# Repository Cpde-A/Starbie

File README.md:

# Starbie
This is Starbie. A fun, playful, companion. It keeps you company when your alone. It helps you with your anxiety. Use it well.

It uses an ESP32 C3 and a sensor to detect when you are near. You interact with Starbie on a screen and play with it using buttons.

Schematic

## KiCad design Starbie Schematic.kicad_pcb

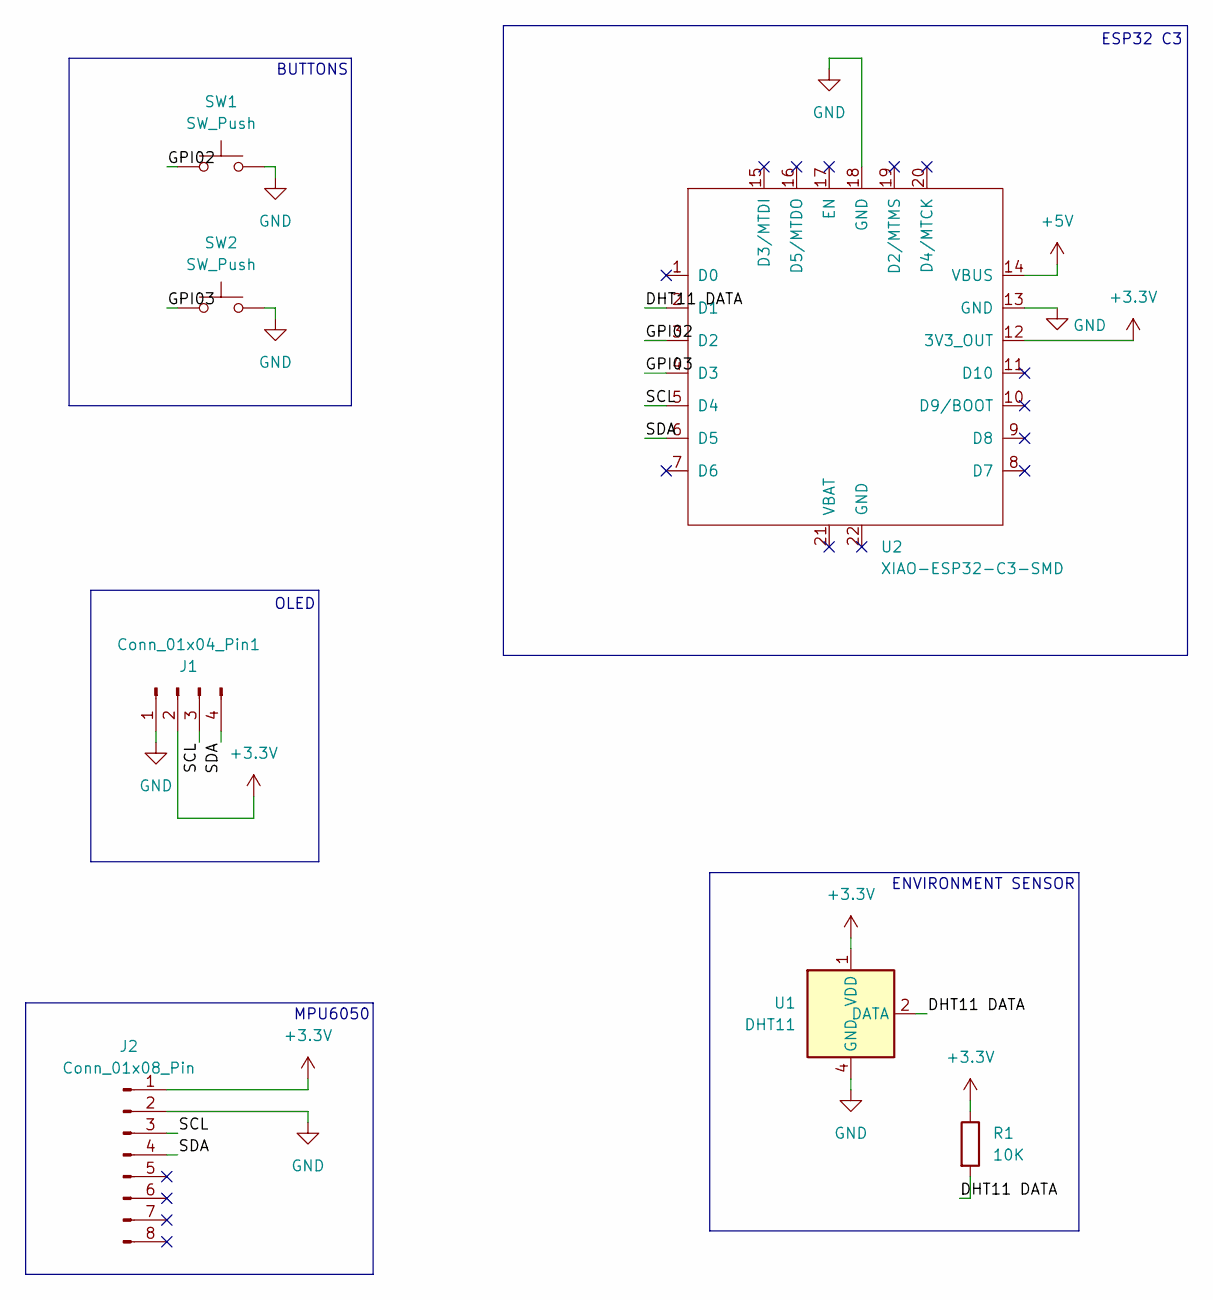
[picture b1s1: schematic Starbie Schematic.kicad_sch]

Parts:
Conn_01x04_Pin1: J1; Display_128x64_096_I2C
J2: Conn_01x08_Pin; PinHeader_1x08_P2.54mm_Vertical
R1: 10K; R_Axial_DIN0204_L3.6mm_D1.6mm_P7.62mm_Horizontal
SW1, SW2: SW_Push; SW_Cherry_MX_1.00u_PCB
U1: DHT11; Aosong_DHT11_5.5x12.0_P2.54mm
U2: XIAO-ESP32-C3-SMD

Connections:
+3.3V: Conn_01x04_Pin1.2 (Pin_3), J2.1, R1.1, U1.1 (VDD), U2.12 (3V3_OUT)
+5V: U2.14 (VBUS)
/DHT11 DATA: R1.2, U1.2 (DATA), U2.2 (D1)
/GPI02: SW1.1, U2.3 (D2)
/GPI03: SW2.1, U2.4 (D3)
/SCL: Conn_01x04_Pin1.3 (Pin_2), J2.3, U2.5 (D4)
/SDA: Conn_01x04_Pin1.4 (Pin_1), J2.4, U2.6 (D5)
GND: Conn_01x04_Pin1.1 (Pin_4), J2.2, SW1.2, SW2.2, U1.4 (GND), U2.13 (GND), U2.18 (GND)

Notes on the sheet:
ESP32 C3
ENVIRONMENT SENSOR
OLED
MPU6050
BUTTONS

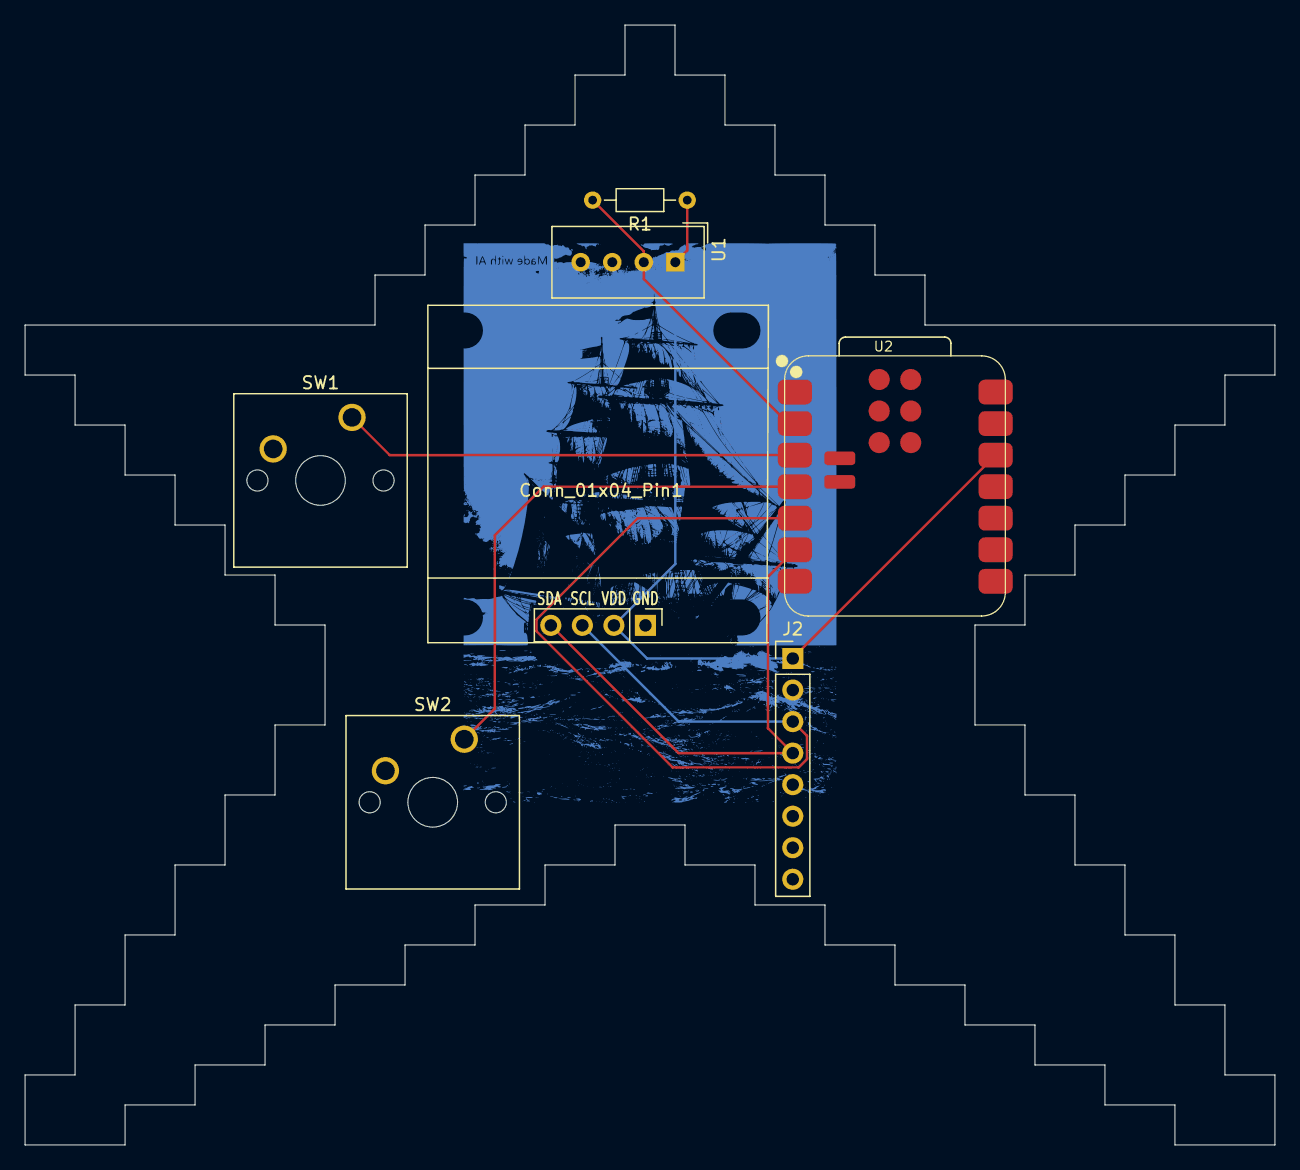
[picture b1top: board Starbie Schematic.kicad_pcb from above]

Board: 2 copper layers, 100.7 x 90.2 mm, 7 parts (0 on the bottom side), 7 nets.
